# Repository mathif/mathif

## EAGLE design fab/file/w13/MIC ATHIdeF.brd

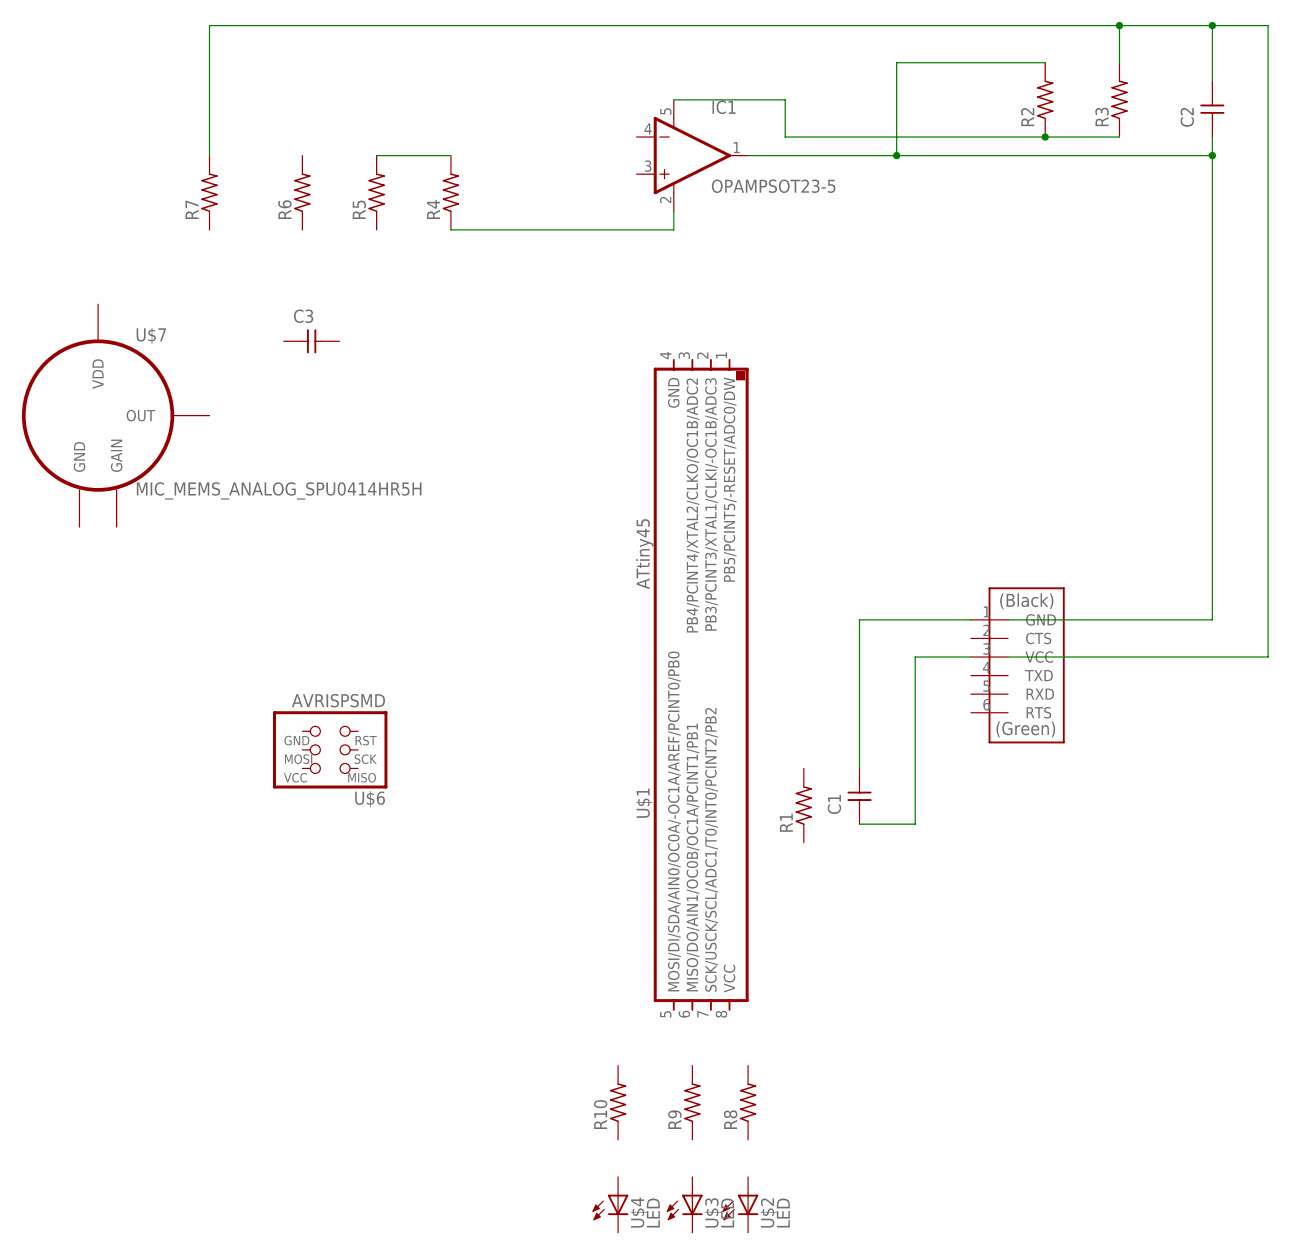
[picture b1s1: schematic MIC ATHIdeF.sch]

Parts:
C1, C2, C3: CAP-UNPOLARIZED; C1206
IC1: OPAMPSOT23-5; SOT23-5
R1, R2, R3, R4, R5, R6, R7, R8, R9, R10: RES-US1206; R1206
U$1: ATTINY45SI; SOIC8
U$2, U$3, U$4: LED; LED1206
U$5: FTDI-SMD-HEADER; 1X06SMD
U$6: AVRISPSMD; 2X03SMD
U$7: MIC_MEMS_ANALOG_SPU0414HR5H

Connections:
GND: U$7.2 (GND)
unnamed: C2.2, R3.2, R7.2
unnamed: C1.1, U$5.3 (VCC)
unnamed: C1.2, U$5.1 (GND)
unnamed: C2.1, IC1.1 (OUT), R2.2
unnamed: IC1.5 (V+), R2.1, R3.1
unnamed: IC1.2 (V-), R4.1
unnamed: R4.2, R5.2
VDD: U$7.1 (VDD)

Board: 2 copper layers, 21 parts (0 on the bottom side), 7 nets, no tracks yet.

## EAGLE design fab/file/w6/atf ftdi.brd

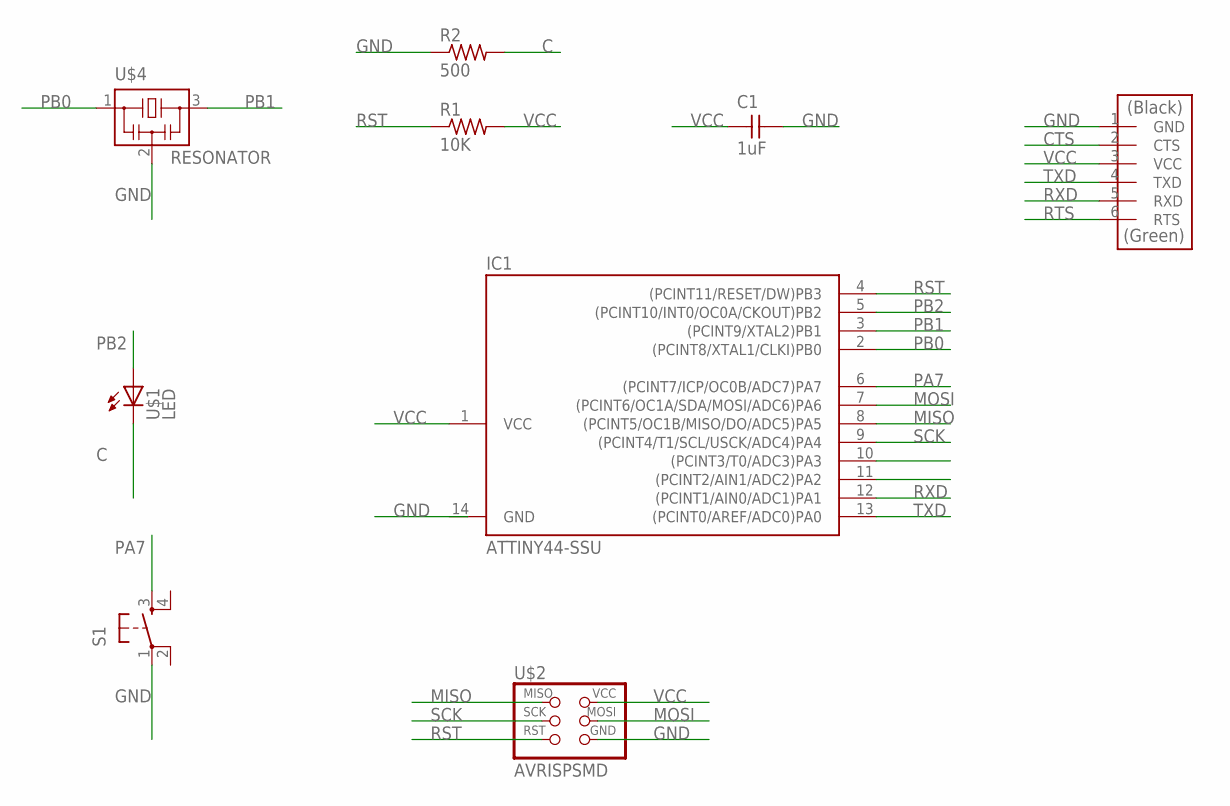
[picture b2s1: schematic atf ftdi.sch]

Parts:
C1: 1uF; C1206
IC1: ATTINY44-SSU; SOIC14
R1: 10K; R1206
R2: 500; R1206
S1: 6MM_SWITCH6MM_SWITCH; 6MM_SWITCH
U$1: LED; LED1206
U$2: AVRISPSMD; 2X03SMD
U$3: FTDI-SMD-HEADER; 1X06SMD
U$4: RESONATOR; EFOBM

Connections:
5: IC1.11 ((PCINT2/AIN1/ADC2)PA2)
C: R2.2, U$1.2 (C)
CTS: U$3.2 (CTS)
GND: C1.2, IC1.14 (GND), R2.1, S1.1, U$2.6 (GND), U$3.1 (GND), U$4.2
MISO: IC1.8 ((PCINT5/OC1B/MISO/DO/ADC5)PA5), U$2.1 (MISO)
MOSI: IC1.7 ((PCINT6/OC1A/SDA/MOSI/ADC6)PA6), U$2.4 (MOSI)
PA7: IC1.6 ((PCINT7/ICP/OC0B/ADC7)PA7), S1.3 (S)
PB0: IC1.2 ((PCINT8/XTAL1/CLKI)PB0), U$4.1
PB1: IC1.3 ((PCINT9/XTAL2)PB1), U$4.3
PB2: IC1.5 ((PCINT10/INT0/OC0A/CKOUT)PB2), U$1.1 (A)
RST: IC1.4 ((PCINT11/RESET/DW)PB3), R1.1, U$2.5 (RST)
RTS: U$3.6 (RTS)
RXD: IC1.12 ((PCINT1/AIN0/ADC1)PA1), U$3.5 (RXD)
SCK: IC1.9 ((PCINT4/T1/SCL/USCK/ADC4)PA4), U$2.3 (SCK)
TXD: IC1.13 ((PCINT0/AREF/ADC0)PA0), U$3.4 (TXD)
VCC: C1.1, IC1.1 (VCC), R1.2, U$2.2 (VCC), U$3.3 (VCC)

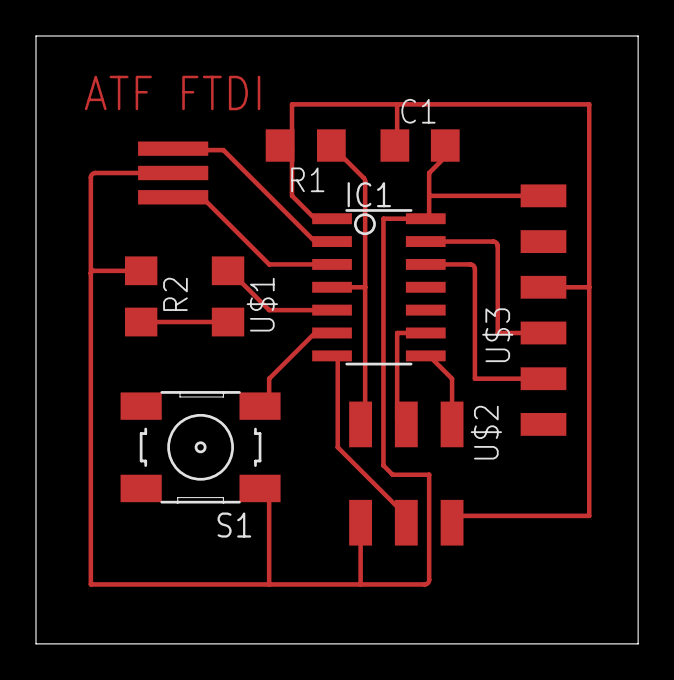
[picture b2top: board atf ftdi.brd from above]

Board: 2 copper layers, 33.5 x 33.8 mm, 9 parts (0 on the bottom side), 13 nets.

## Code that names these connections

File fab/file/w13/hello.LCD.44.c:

#include <avr/io.h>
#include <util/delay.h>
#include <avr/pgmspace.h>

#define output(directions,pin) (directions |= pin) // set port direction for output
#define set(port,pin) (port |= pin) // set port pin
#define clear(port,pin) (port &= (~pin)) // clear port pin
#define pin_test(pins,pin) (pins & pin) // test for port pin
#define bit_test(byte,bit) (byte & (1 << bit)) // test for bit set

#define LCD_port PORTA
#define LCD_direction DDRA
#define DB7 (1 << PA0)
#define DB6 (1 << PA1)
#define DB5 (1 << PA2)
#define DB4 (1 << PA3)
#define E (1 << PA4)
#define RS (1 << PA5)

#define long_delay() _delay_ms(1000) // delay before redraw
#define lcd_delay() _delay_ms(10) // delay between commands
#define strobe_delay() _delay_us(1) // delay for strobe

//
// lcd_putchar
//    put character in lcdbyte
//
void lcd_putchar(char lcdbyte) {
   //
   // set RS for data
   // 
   set(LCD_port, RS);
   //
   // output high nibble
   //
   if bit_test(lcdbyte, 7)
      set(LCD_port, DB7);
   else
      clear(LCD_port, DB7);
   if bit_test(lcdbyte, 6)
      set(LCD_port, DB6);
   else
      clear(LCD_port, DB6);
   if bit_test(lcdbyte, 5)
      set(LCD_port, DB5);
   else
      clear(LCD_port, DB5);
   if bit_test(lcdbyte, 4)
      set(LCD_port, DB4);
   else
      clear(LCD_port, DB4);
   //
   // strobe E
   //
   strobe_delay();
   set(LCD_port, E);
   strobe_delay();
   clear(LCD_port, E);
   //
   // wait
   //
   lcd_delay();
   //
   // output low nibble
   //
   if bit_test(lcdbyte, 3)
      set(LCD_port, DB7);
   else
      clear(LCD_port, DB7);
   if bit_test(lcdbyte, 2)
      set(LCD_port, DB6);
   else
      clear(LCD_port, DB6);
   if bit_test(lcdbyte, 1)
      set(LCD_port, DB5);
   else
      clear(LCD_port, DB5);
   if bit_test(lcdbyte, 0)
      set(LCD_port, DB4);
   else
      clear(LCD_port, DB4);
   //
   // strobe E
   //
   strobe_delay();
   set(LCD_port, E);
   strobe_delay();
   clear(LCD_port, E);
   //
   // wait and return
   //
   lcd_delay();
   }
//
// lcd_putcmd
//    put command in lcdbyte
//
void lcd_putcmd(char lcdbyte) {
   //
   // clear RS for command
   // 
   clear(LCD_port, RS);
   //
   // output command bits
   //
   PORTA = lcdbyte;
   //
   // strobe E
   //
   strobe_delay();
   set(LCD_port, E);
   strobe_delay();
   clear(LCD_port, E);
   //
   // wait and return
   //
   lcd_delay();
   }
//
// lcd_putstring
//    put a null-terminated string in flash
//
void lcd_putstring(PGM_P message) {
   static uint8_t index;
   static char chr;
   index = 0;
   while (1) {
      chr = pgm_read_byte(&(message[index]));
      if (chr == 0)
         return;
      lcd_putchar(chr);
      ++index;
      }
   }
//
// lcd_init
//    initialize the LCD
//
void lcd_init() {
   //
   // power-up delay
   //
   lcd_delay();
   //
   // initialization sequence
   //
   lcd_putcmd(DB5+DB4);
   lcd_putcmd(DB5+DB4);
   lcd_putcmd(DB5+DB4);
   //
   // 4-bit interface
   //
   lcd_putcmd(DB5);
   //
   // two lines, 5x7 font
   //
   lcd_putcmd(DB5);
   lcd_putcmd(DB7);
   //
   // display on
   //
   lcd_putcmd(0);
   lcd_putcmd(DB7+DB6+DB5);
   //
   // entry mode
   //
   lcd_putcmd(0);
   lcd_putcmd(DB6+DB5);
   }

int main(void) {
   //
   // main
   //
   // set clock divider to /1
   //
   CLKPR = (1 << CLKPCE);
   CLKPR = (0 << CLKPS3) | (0 << CLKPS2) | (0 << CLKPS1) | (0 << CLKPS0);
   //
   // initialize LCD pins
   //
   clear(LCD_port, DB7);
   output(LCD_direction, DB7);
   clear(LCD_port, DB6);
   output(LCD_direction, DB6);
   clear(LCD_port, DB5);
   output(LCD_direction, DB5);
   clear(LCD_port, DB4);
   output(LCD_direction, DB4);
   clear(LCD_port, E);
   output(LCD_direction, E);
   clear(LCD_port, RS);
   output(LCD_direction, RS);
   //
   // initialize LCD
   //
   lcd_init();
   //
   // main loop
   //
   while (1) {
      // 
      // go to zero position
      //
      lcd_putcmd(0);
      lcd_putcmd(DB5);
      //
      // print first line from flash
      //
      static const char line1[] PROGMEM = "Kerarla : Kerala";
      lcd_putstring((PGM_P) line1);
      //
      // move to second line
      //
      lcd_putcmd(DB7+DB6);
      lcd_putcmd(0);
      //
      // print second line from flash
      //
      static const char line2[] PROGMEM = "own country";
      lcd_putstring((PGM_P) line2);
      //
      // pause
      //
      long_delay();
      //
      // clear display
      //
      lcd_putcmd(0);
      lcd_putcmd(DB4);
      }
   }

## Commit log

2015-10-29 hai...
2015-10-29 my world
2015-11-09 first uplaoad with francisco
2015-11-09 not reachd fransico target
2015-11-09 target 3 notreacd week3
2015-11-09 first imge upload
2015-11-09 repush
2015-11-09 repush after delet
2015-11-09 from home
2015-11-10 link update
2015-11-11 image leveling
2015-11-11 program
2015-11-11 check
2015-11-12 html
2015-11-12 push
2015-11-18 push avunilla
2016-02-17 Replace master branch with page content via GitHub
2016-09-06 Create CNAME
2016-12-02 push avun
2017-08-07 duse
2017-08-22 payment
2018-02-11 Update CNAME
